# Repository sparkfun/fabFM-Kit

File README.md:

**NOTE:** *This product has been retired from our catalog. If you are looking for more up-to-date info, please check out some of these resources to see how other users are still hacking and improving on this product.*
* *[SparkFun Forum](https://forum.sparkfun.com/)*
* *[IRC Channel](https://www.sparkfun.com/news/263)*

FabFM Radio Kit
===============

[  
*FabFM Radio Kit (KIT-11043)*](https://www.sparkfun.com/products/11043)

The FabFM is a stylish FM radio kit that can be built with just basic soldering tools. The PCB is all PTH, meaning that even a beginner solderer can put this kit together with a little time. The wooden, laser cut frame doesn't take any tools or glue to put together, each part press-fits into another. Once assembled the FabFM Radio Kit produces a fully functioning, old-school style FM radio.

[*See the wiki for assembly instuctions.*](https://github.com/sparkfun/fabFM-Kit/wiki)

Repository Contents
-------------------

* **/enclosure** - Vector files for the enclosure
* **/firmware** - Arduino sketch that is loaded onto the ATMega328
* **/hardware** - Eagle PCB layout files

License Information
-------------------

All contents of this repository are released under [Creative Commons Share-alike 3.0](http://creativecommons.org/licenses/by-sa/3.0/).

Authors: Aaron Weiss @ SparkFun Electonics, Original Design by David Mellis and Dana Gordon

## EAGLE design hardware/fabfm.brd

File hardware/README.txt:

See the commit comments for version information.

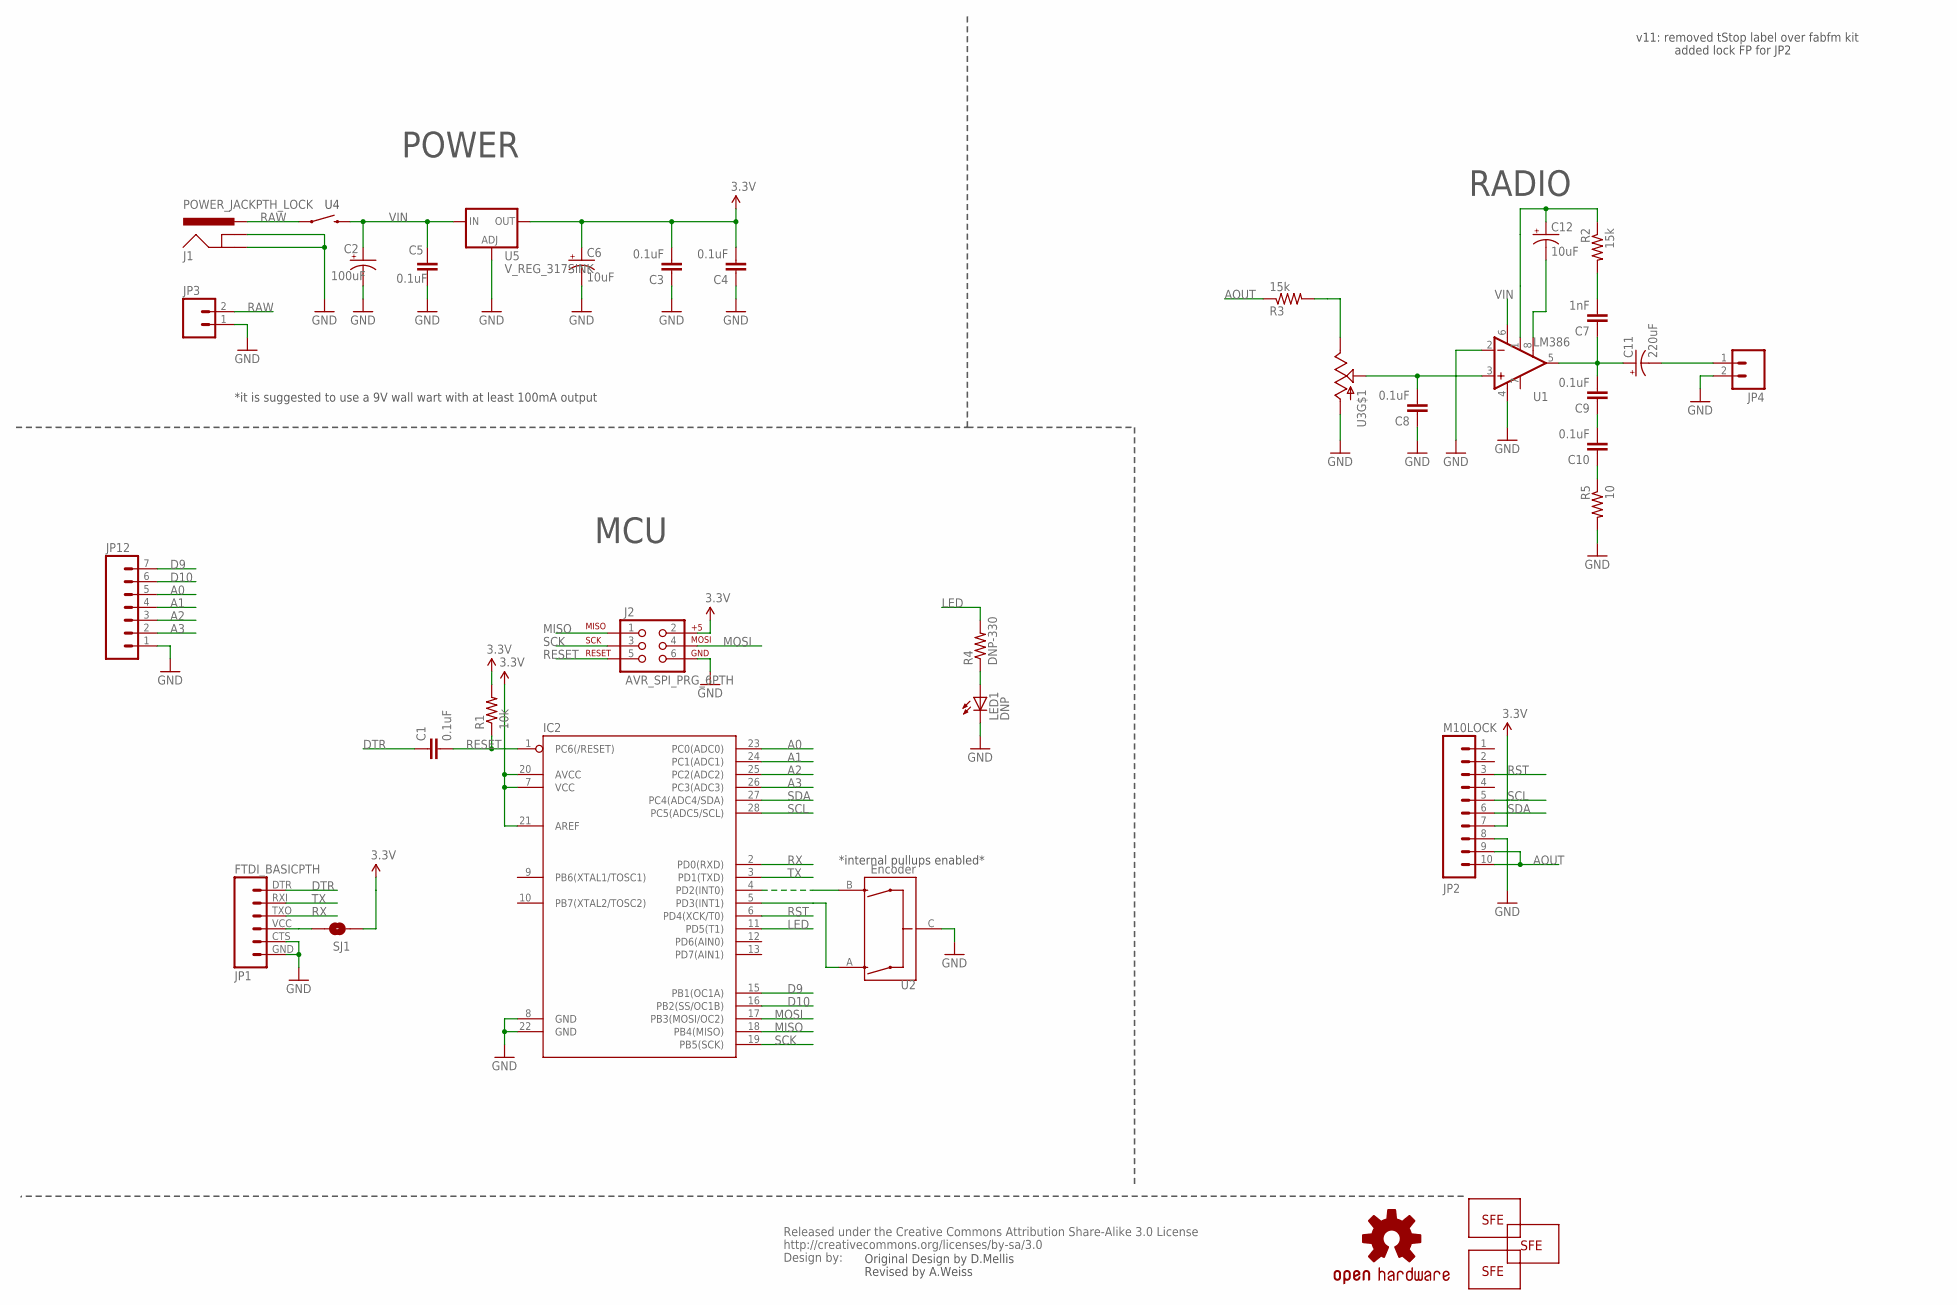
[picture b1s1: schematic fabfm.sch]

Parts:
C1, C3, C4, C5, C8, C9, C10: 0.1uF; CAP-PTH-SMALL-KIT
C2: 100uF; CPOL-RADIAL-100UF-25V
C6, C12: 10uF; CPOL-RADIAL-10UF-25V
C7: 1nF; CAP-PTH-SMALL-KIT
C11: 220uF; CPOL-RADIAL-100UF-25V
IC2: ATMEGA328P_PDIP_EZ_PB0; DIL28-EZ-PB0
J1: POWER_JACKPTH_LOCK; POWER_JACK_PTH_LOCK
J2: AVR_SPI_PRG_6PTH; 2X3
JP1: FTDI_BASICPTH; FTDI_BASIC
JP2: M10LOCK; 1X10_LOCK
JP3: M02PTH; 1X02
JP4: M02PTH4; 1X02_XTRA_BIG
JP8: LOGO-SFESK; SFE-LOGO-FLAME
JP9, JP11: LOGO-SFENEW; SFE-NEW-WEBLOGO
JP12: M07; 1X07
LED1: DNP; LED3MM
R1: 10k; AXIAL-0.4
R2, R3: 15k; AXIAL-0.4
R4: DNP-330; AXIAL-0.4
R5: 10; AXIAL-0.4
SJ1: SOLDERJUMPERNO; SJ_2S-NO
U1: LM386; DIP08
U2: Encoder; ENCODER-16MM-QUAD
U3: POT_SWITCHPOT_PTH_SWITCH; POT_PTH_SWITCH
U5: V_REG_317SINK; TO220-ADJ
U$1: OSHW-LOGOS; OSHW-LOGO-S
U$2: CREATIVE_COMMONS

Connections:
3.3V: C3.2, C4.2, C6.1 (+), IC2.7 (VCC), IC2.20 (AVCC), IC2.21 (AREF), J2.2, JP2.7, R1.P$2 (2), SJ1.1, U5.OUT
A: IC2.5 (PD3(INT1)), U2.A
A0: IC2.23 (PC0(ADC0)), JP12.5
A1: IC2.24 (PC1(ADC1)), JP12.4
A2: IC2.25 (PC2(ADC2)), JP12.3
A3: IC2.26 (PC3(ADC3)), JP12.2
AOUT: JP2.9, JP2.10, R3.P$1 (1)
B: IC2.4 (PD2(INT0)), U2.B
D9: IC2.15 (PB1(OC1A)), JP12.7
D10: IC2.16 (PB2(SS/OC1B)), JP12.6
DTR: C1.1, JP1.DTR (1)
GND: C2.2 (-), C3.1, C4.1, C5.1, C6.2 (-), C8.1, IC2.8 (GND), IC2.22 (GND), J1.GND, J1.GNDBREAK, J2.6, JP1.CTS (5), JP1.GND (6), JP2.8, JP3.1, JP4.2, JP12.1, LED1.K (C), R5.P$2 (2), U1.2 (-IN), U1.4 (V-), U2.C, U3.1 (A), U5.ADJ
LED: IC2.11 (PD5(T1)), R4.P$2 (2)
MISO: IC2.18 (PB4(MISO)), J2.1
MOSI: IC2.17 (PB3(MOSI/OC2)), J2.4
unnamed: LED1.A, R4.P$1 (1)
unnamed: C8.2, U1.3 (+IN), U3.2 (S)
unnamed: C7.1, C9.2, C11.1 (+), U1.5 (OUT)
unnamed: C12.1 (+), R2.P$1 (1), U1.1 (GAIN)
unnamed: C11.2 (-), JP4.1
unnamed: C9.1, C10.2
unnamed: C10.1, R5.P$1 (1)
unnamed: C12.2 (-), U1.8 (GAIN)
unnamed: C7.2, R2.P$2 (2)
unnamed: R3.P$2 (2), U3.3 (E)
unnamed: JP1.VCC (4), SJ1.2
RAW: J1.PWR, JP3.2, U3.S1 (1)
RESET: C1.2, IC2.1 (PC6(/RESET)), J2.5, R1.P$1 (1)
RST: IC2.6 (PD4(XCK/T0)), JP2.3
RX: IC2.2 (PD0(RXD)), JP1.TXO (3)
SCK: IC2.19 (PB5(SCK)), J2.3
SCL: IC2.28 (PC5(ADC5/SCL)), JP2.5
SDA: IC2.27 (PC4(ADC4/SDA)), JP2.6
TX: IC2.3 (PD1(TXD)), JP1.RXI (2)
VIN: C2.1 (+), C5.2, U1.6 (V+), U3.S2 (2), U5.IN

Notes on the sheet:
Original Design by D.Mellis
POWER
MCU
RADIO
Revised by A.Weiss
*internal pullups enabled*
*it is suggested to use a 9V wall wart with at least 100mA output
v11: removed tStop label over fabfm kit
added lock FP for JP2

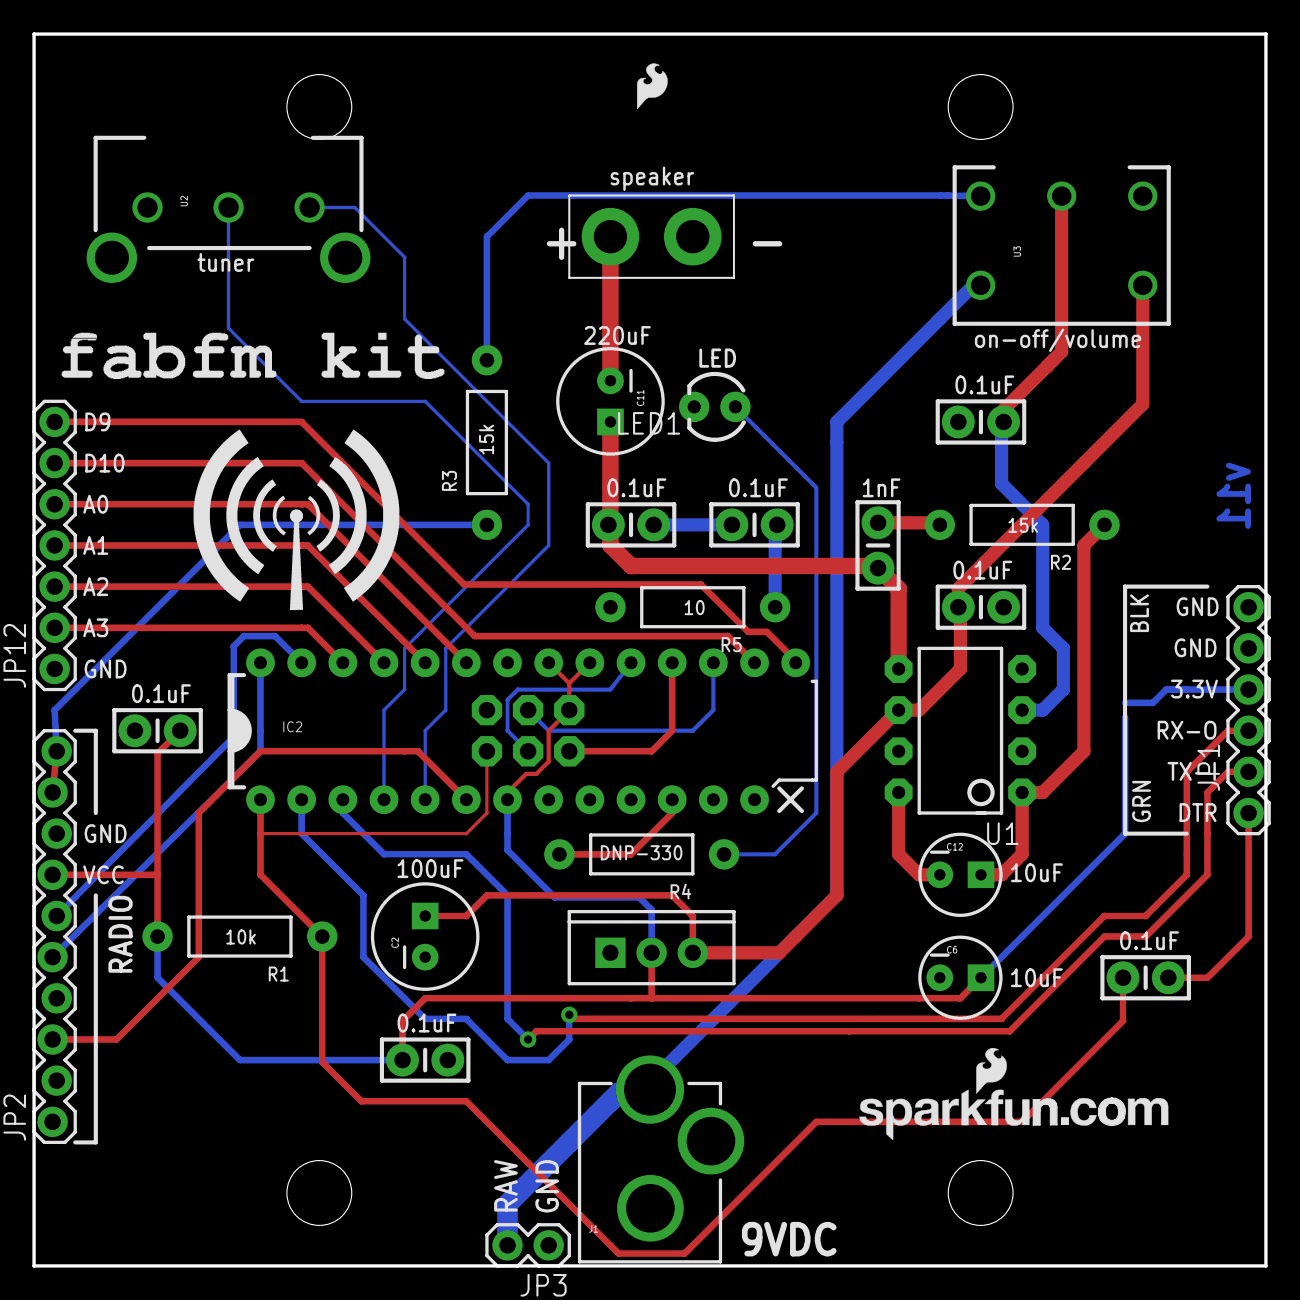
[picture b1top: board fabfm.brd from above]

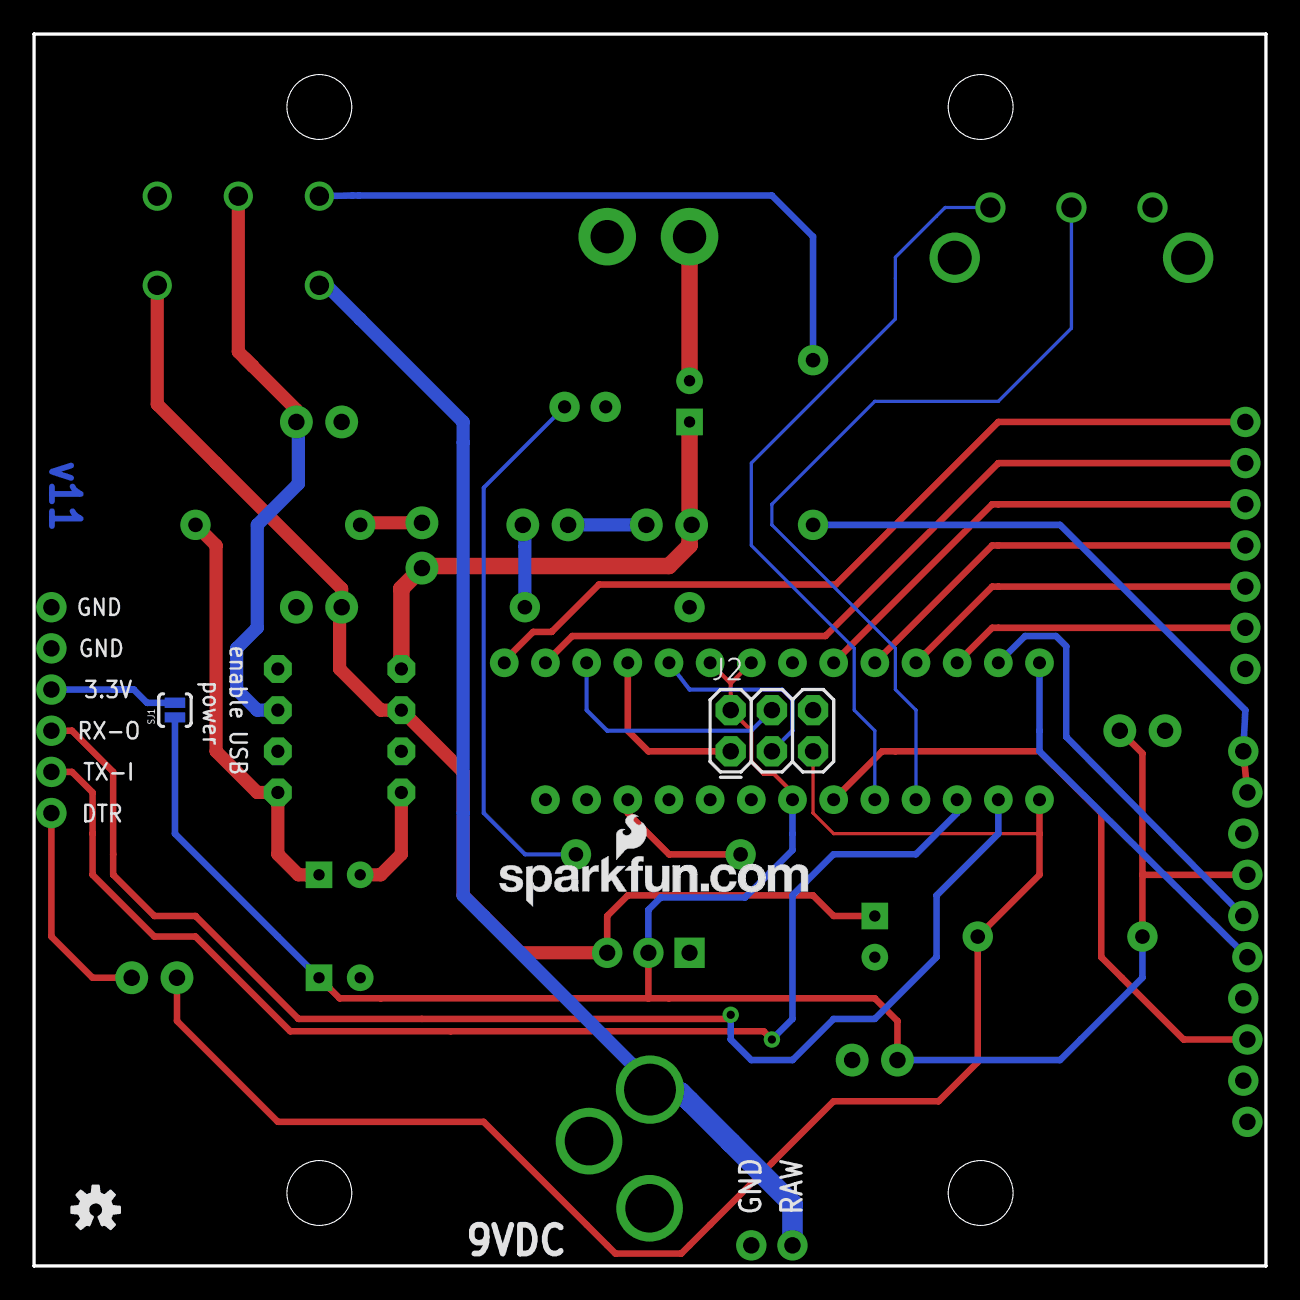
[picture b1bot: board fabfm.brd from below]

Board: 2 copper layers, 76.0 x 76.0 mm, 36 parts (4 on the bottom side), 35 nets.

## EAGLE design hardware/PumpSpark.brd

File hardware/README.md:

These are the Eagle PCB files for the fabfm.

See the commit comments for version information.

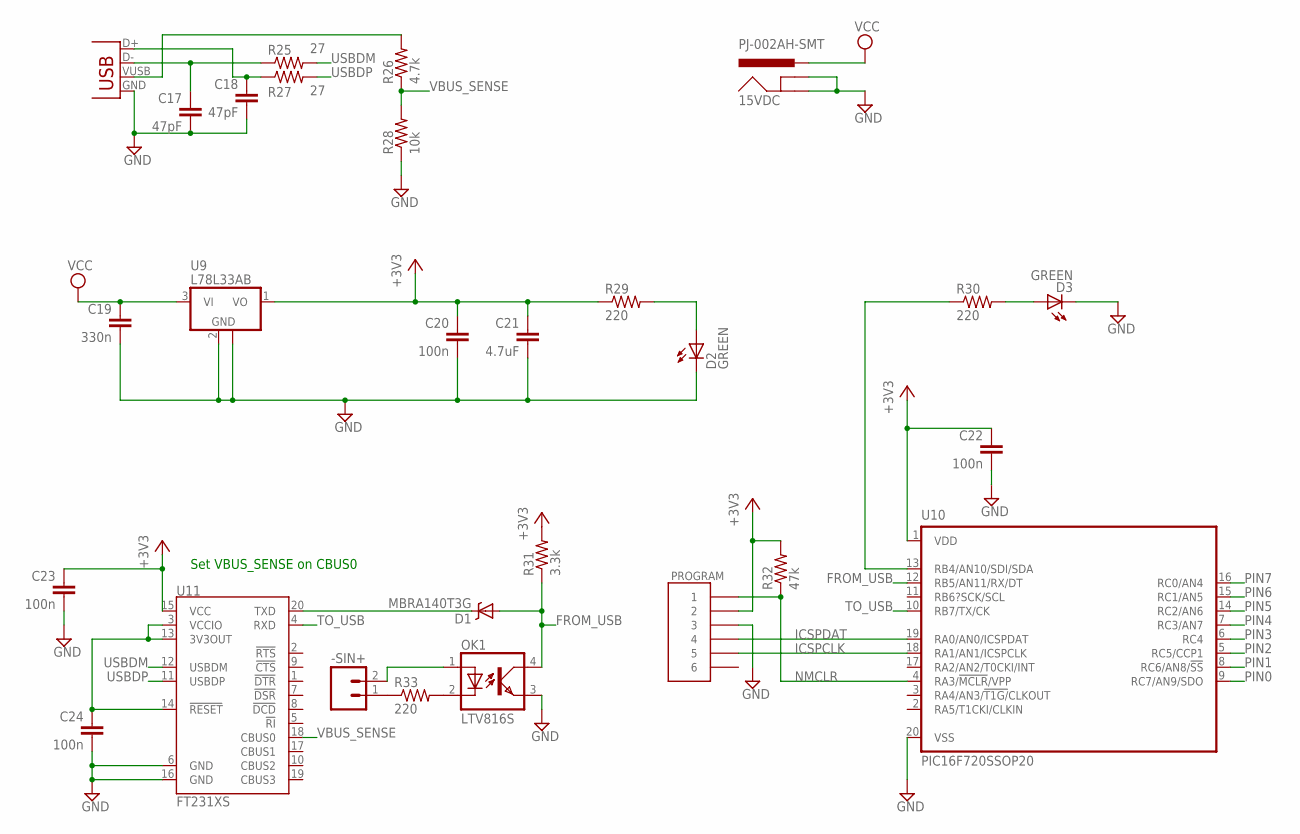
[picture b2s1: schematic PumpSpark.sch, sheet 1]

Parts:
15VDC: PJ-002AH-SMT; POWER_JACK_SMD
-SIN+: M02LOCK; 1X02_LOCK
C17, C18: 47pF; 0603-CAP
C19: 330n; 0603-CAP
C20, C22, C23, C24: 100n; 0603-CAP
C21: 4.7uF; 0603-CAP
D1: MBRA140T3G; SMA-DIODE
D2, D3: GREEN; LED-0603
OK1: LTV816S; SMD4
PROGRAM: HEADER-6MOLEX-KK; MOLEX-KK-HEADER-6
R25, R27: 27; 0603-RES
R26: 4.7k; 0603-RES
R28: 10k; 0603-RES
R29, R30, R33: 220; 0603-RES
R31: 3.3k; 0603-RES
R32: 47k; 0603-RES
U9: L78L33AB; SOT89
U10: PIC16F720SSOP20; SSOP20
U11: FT231XS; SSOP20_L
USB: USB-B-S; USB-B-SMT

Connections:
+3V3: C20.1, C21.1, C22.1, C23.1, PROGRAM.2, R29.1, R31.2, R32.2, U9.1 (VO), U10.1 (VDD), U11.15 (VCC)
FROM_USB: D1.A, OK1.4 (COL), R31.1, U10.12 (RB5/AN11/RX/DT)
GND: 15VDC.GND (GNDBREAK), 15VDC.P$4 (GND), C17.2, C18.2, C19.2, C20.2, C21.2, C22.2, C23.2, C24.2, D2.C, D3.C, OK1.3 (EMIT), PROGRAM.3, R28.1, U9.2 (GND), U9.2@1 (GND), U10.20 (VSS), U11.6 (GND), U11.16 (GND), USB.GND; also elsewhere on the board
ICSPCLK: PROGRAM.5, U10.18 (RA1/AN1/ICSPCLK)
ICSPDAT: PROGRAM.4, U10.19 (RA0/AN0/ICSPDAT)
unnamed: OK1.2 (C), R33.2
unnamed: D1.C, U11.20 (TXD)
unnamed: C24.1, U11.3 (VCCIO), U11.13 (3V3OUT), U11.14 (!RESET)
unnamed: D2.A, R29.2
unnamed: D3.A, R30.2
unnamed: R26.2, USB.VUSB (VBUS)
unnamed: R30.1, U10.13 (RB4/AN10/SDI/SDA)
unnamed: C17.1, R25.1, USB.D-
unnamed: C18.1, R27.1, USB.D+
unnamed: -SIN+.1, R33.1
unnamed: -SIN+.2, OK1.1 (A)
NMCLR: PROGRAM.1, R32.1, U10.4 (RA3/!MCLR!/VPP)
PIN0: U10.9 (RC7/AN9/SDO); also elsewhere on the board
PIN1: U10.8 (RC6/AN8/!SS); also elsewhere on the board
PIN2: U10.5 (RC5/CCP1); also elsewhere on the board
PIN3: U10.6 (RC4); also elsewhere on the board
PIN4: U10.7 (RC3/AN7); also elsewhere on the board
PIN5: U10.14 (RC2/AN6); also elsewhere on the board
PIN6: U10.15 (RC1/AN5); also elsewhere on the board
PIN7: U10.16 (RC0/AN4); also elsewhere on the board
TO_USB: U10.10 (RB7/TX/CK), U11.4 (RXD)
USBDM: R25.2, U11.12 (USBDM)
USBDP: R27.2, U11.11 (USBDP)
VBUS_SENSE: R26.1, R28.2, U11.18 (CBUS0)
VCC: 15VDC.VIN0 (PWR), C19.1, U9.3 (VI); also elsewhere on the board

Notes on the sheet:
Set VBUS_SENSE on CBUS0

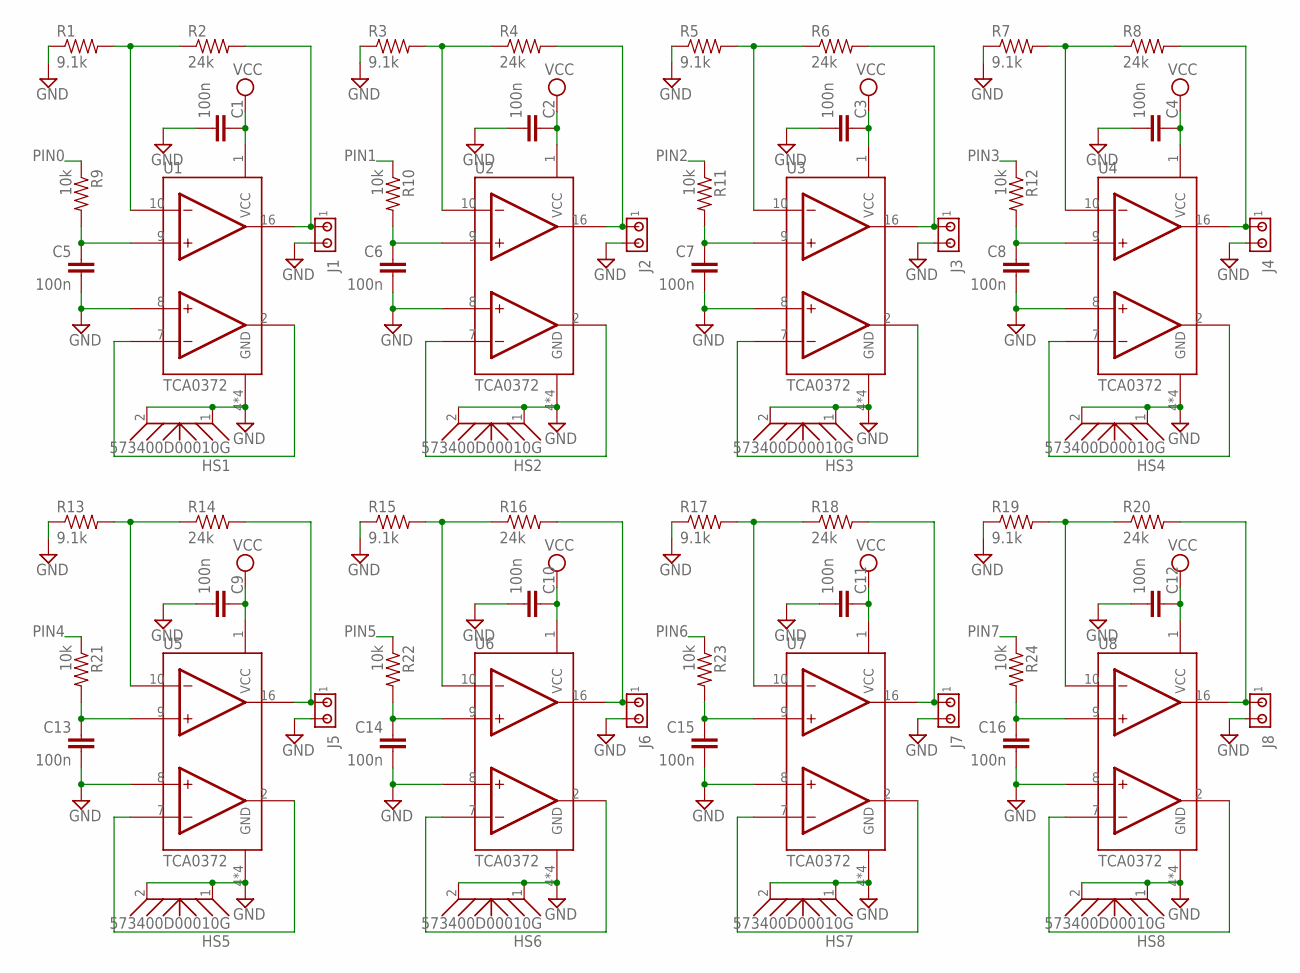
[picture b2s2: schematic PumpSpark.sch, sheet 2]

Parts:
C1, C2, C3, C4, C5, C6, C7, C8, C9, C10, C11, C12, C13, C14, C15, C16: 100n; 0603-CAP
HS1, HS2, HS3, HS4, HS5, HS6, HS7, HS8: 573400D00010G
J1, J2, J3, J4, J5, J6, J7, J8: MTA02-100; 10X02MTA
R1, R3, R5, R7, R13, R15, R17, R19: 9.1k; 0603-RES
R2, R4, R6, R8, R14, R16, R18, R20: 24k; 0603-RES
R9, R10, R11, R12, R21, R22, R23, R24: 10k; 0603-RES
U1, U2, U3, U4, U5, U6, U7, U8: TCA0372; SO16W

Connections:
GND: C1.2, C2.2, C3.2, C4.2, C5.2, C6.2, C7.2, C8.2, C9.2, C10.2, C11.2, C12.2, C13.2, C14.2, C15.2, C16.2, HS1.1 (LEFT), HS1.2 (RIGHT), HS2.1 (LEFT), HS2.2 (RIGHT), HS3.1 (LEFT), HS3.2 (RIGHT), HS4.1 (LEFT), HS4.2 (RIGHT), HS5.1 (LEFT), HS5.2 (RIGHT), HS6.1 (LEFT), HS6.2 (RIGHT), HS7.1 (LEFT), HS7.2 (RIGHT), HS8.1 (LEFT), HS8.2 (RIGHT), J1.2, J2.2, J3.2, J4.2, J5.2, J6.2, J7.2, J8.2, R1.1, R3.1, R5.1, R7.1, R13.1, R15.1, R17.1, R19.1, U1.4 (GND), U1.5 (GND), U1.8 (+INB), U1.12 (GND), U1.13 (GND), U2.4 (GND), U2.5 (GND), U2.8 (+INB), U2.12 (GND), U2.13 (GND), U3.4 (GND), U3.5 (GND), U3.8 (+INB), U3.12 (GND), U3.13 (GND), U4.4 (GND), U4.5 (GND), U4.8 (+INB), U4.12 (GND), U4.13 (GND), U5.4 (GND), U5.5 (GND), U5.8 (+INB), U5.12 (GND), U5.13 (GND), U6.4 (GND), U6.5 (GND), U6.8 (+INB), U6.12 (GND), U6.13 (GND), U7.4 (GND), U7.5 (GND), U7.8 (+INB), U7.12 (GND), U7.13 (GND), U8.4 (GND), U8.5 (GND), U8.8 (+INB), U8.12 (GND), U8.13 (GND); also elsewhere on the board
unnamed: J2.1, R4.2, U2.16 (OUTA)
unnamed: R3.2, R4.1, U2.10 (-INA)
unnamed: C5.1, R9.2, U1.9 (+INA)
unnamed: U2.2 (OUTB), U2.7 (-INB)
unnamed: J3.1, R6.2, U3.16 (OUTA)
unnamed: R5.2, R6.1, U3.10 (-INA)
unnamed: C6.1, R10.2, U2.9 (+INA)
unnamed: U3.2 (OUTB), U3.7 (-INB)
unnamed: J4.1, R8.2, U4.16 (OUTA)
unnamed: R7.2, R8.1, U4.10 (-INA)
unnamed: C7.1, R11.2, U3.9 (+INA)
unnamed: U4.2 (OUTB), U4.7 (-INB)
unnamed: J5.1, R14.2, U5.16 (OUTA)
unnamed: R13.2, R14.1, U5.10 (-INA)
unnamed: C8.1, R12.2, U4.9 (+INA)
unnamed: U5.2 (OUTB), U5.7 (-INB)
unnamed: J6.1, R16.2, U6.16 (OUTA)
unnamed: R15.2, R16.1, U6.10 (-INA)
unnamed: C13.1, R21.2, U5.9 (+INA)
unnamed: U6.2 (OUTB), U6.7 (-INB)
unnamed: J7.1, R18.2, U7.16 (OUTA)
unnamed: R17.2, R18.1, U7.10 (-INA)
unnamed: C14.1, R22.2, U6.9 (+INA)
unnamed: J1.1, R2.2, U1.16 (OUTA)
unnamed: R1.2, R2.1, U1.10 (-INA)
unnamed: C15.1, R23.2, U7.9 (+INA)
unnamed: U1.2 (OUTB), U1.7 (-INB)
unnamed: U7.2 (OUTB), U7.7 (-INB)
unnamed: J8.1, R20.2, U8.16 (OUTA)
unnamed: R19.2, R20.1, U8.10 (-INA)
unnamed: C16.1, R24.2, U8.9 (+INA)
unnamed: U8.2 (OUTB), U8.7 (-INB)
PIN0: R9.1; also elsewhere on the board
PIN1: R10.1; also elsewhere on the board
PIN2: R11.1; also elsewhere on the board
PIN3: R12.1; also elsewhere on the board
PIN4: R21.1; also elsewhere on the board
PIN5: R22.1; also elsewhere on the board
PIN6: R23.1; also elsewhere on the board
PIN7: R24.1; also elsewhere on the board
VCC: C1.1, C2.1, C3.1, C4.1, C9.1, C10.1, C11.1, C12.1, U1.1 (VCC), U2.1 (VCC), U3.1 (VCC), U4.1 (VCC), U5.1 (VCC), U6.1 (VCC), U7.1 (VCC), U8.1 (VCC); also elsewhere on the board

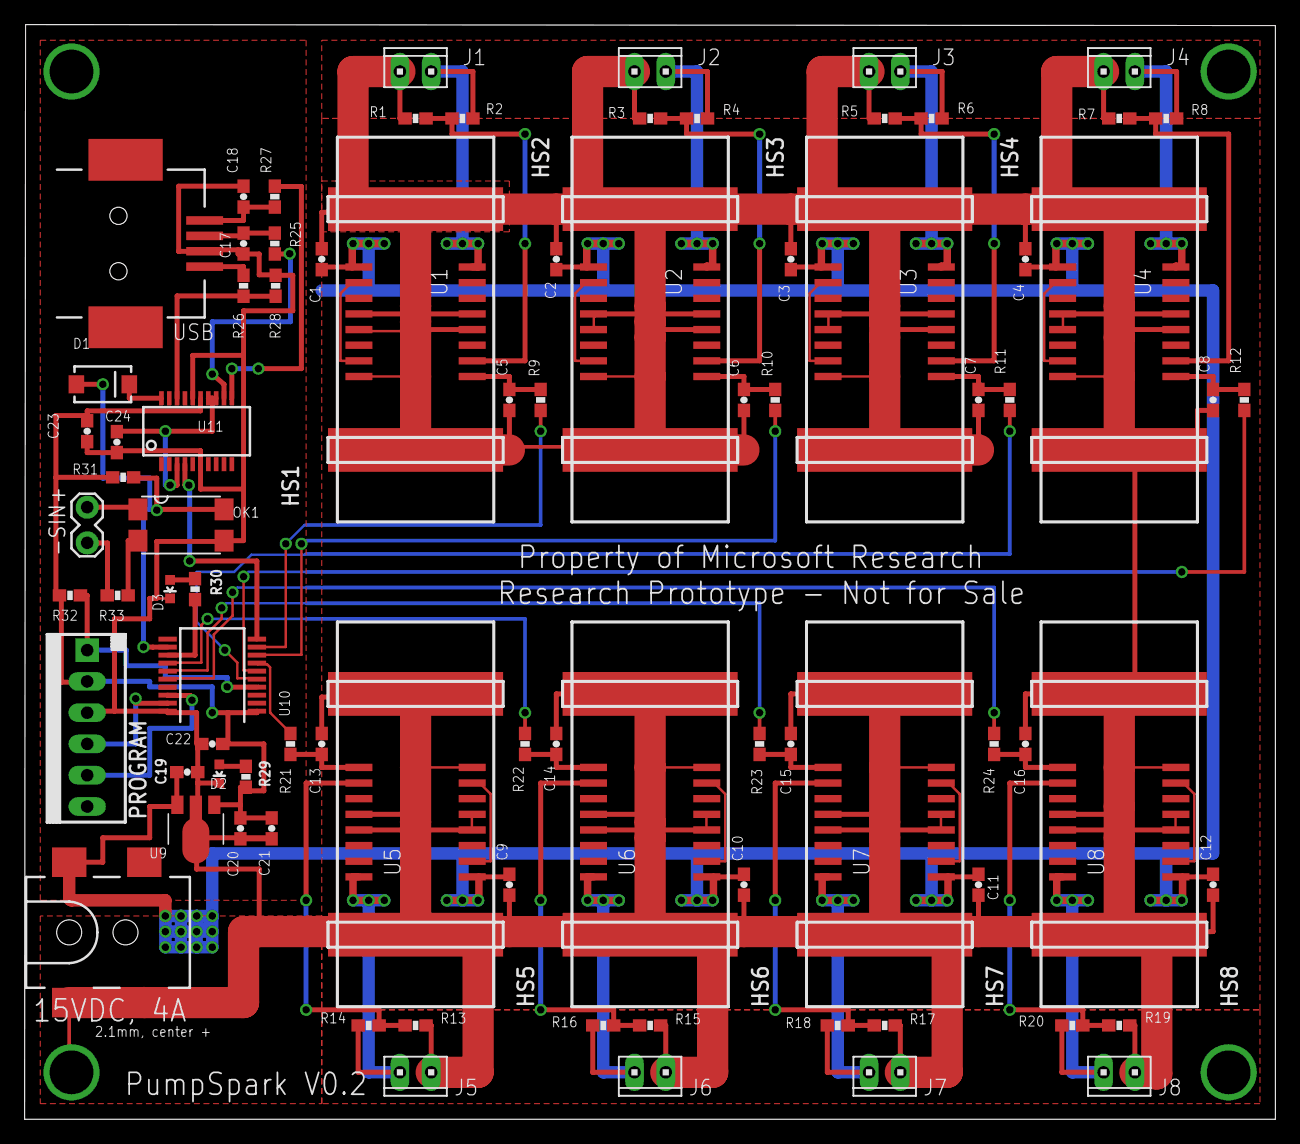
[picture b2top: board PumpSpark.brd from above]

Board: 2 copper layers, 101.6 x 88.9 mm, 92 parts (0 on the bottom side), 62 nets.

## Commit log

2012-10-23 v10
    first
2012-11-29 added enclosure files
    production grade
2012-12-04 v11
    -fixed silk mistake
    -added locking FP for radio module
2012-12-05 v10
    first firmware commit
2012-12-05 v10
    added hex file
2012-12-06 v11
    -added full volume
    -removed version number from ino and hex names
2012-12-06 v10
    -added veneer template
    -removed version number from files
2012-12-06 v10
    added readme
2012-12-06 v10
    edited readme
2012-12-14 veneer sizes adjusted
2012-12-18 edited fabric_template
    -changed file name
    -added notes and more measurements
2012-12-27 enclosure strut openings increased
    to account for changes in wood thickness, I increased the size of all of
    the holes the struts fit into
2013-01-15 changed to md readmes
2013-01-29 Update firmware/README.md
    changed link to Si4703 lib
2013-03-07 cleaning up the readme, adding photo and links, etc.
2013-03-11 Added interrupt support for encoder.
    This fixes the four click reading of the encoder. The encoder is now
    correctly read every click. Also removed link to dropbox copy of library
    (does not compile).
2013-03-11 Change to direct channel contron.
    This removes seek and replaces it with direct channel control. This is
    the type of control I would expect from an analog radio/analog knob. I
    find it is easier to find the station that I am looking for. Currently
    steps 200kHz so works with US only.
2013-03-11 Updated operation instructions.
2013-03-11 An attempt at adding internationalization control.
    I added ability to change how the module is setup (US vs. Europe). These
    changes also require the Si4703 library to be updated. We need to repo
    the Si4703 library.
2013-03-14 firmware changes
    changed version txt in code, commented out up and down print statements
2013-05-01 proto files for collaborator
    -collabs version number is v2
    -needs aesthetic cleanup
2013-05-01 Revert "proto files for collaborator"
    This reverts commit 7e2bf316ebb5f1758cee9bcbaeecd761c46ab435.

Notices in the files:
parts and their libraries:
SparkFun-Connectors: Licensing: CC v3.0 Share-Alike You are welcome to use this library for commercial purposes.
SparkFun: Released under the Creative Commons Attribution Share-Alike 3.0 License
